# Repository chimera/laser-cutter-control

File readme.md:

# Chimera Laser Cutter Control

**Responsible Adult**: [Randy Hall](https://github.com/randybuildsthings)

This Chimera project provides the project (circuit board, bill of materials, etc.) to provide a Mach3/LinuxCNC capable controller board to drive the laser + the stepper motors that position the cutting beam.

This project borrows *heavily* (read: hours of looking over a PDF schematic) of the very excellent but out-of-stock Laser Cutter Converter board that Chris Jones of [Chris' Circuits](http://www.chriscircuits.com) successfully made and then sold out of repeatedly thanks to Hack-A-Day in 2013.

Well, it's almost 2015 and he doesn't seem to be making it any more. Enter the Chimera!

## Ew, EAGLE CAD

Yeah, it's EAGLE CAD. This design works entirely in their free tier, using just two layers and within the size constraints. We might consider moving it to KiCAD or another PCB layout tool, but for now, it's this.

This project was built from scratch using EAGLE CAD 7. We don't expect that it will work on previous version of the program.

## But, what do I do with this?

Ultimately, we will provide packaged and tagged releases of the Gerber and Excellon files for a given revision. Then you can take those files to your favorite PCB fab and get them made.

For now, you can load up whatever version of EAGLE CAD you can find, and open the `.SCH` and `.BRD` files into the software. Behold! The masterpiece. Now you can use the CAM batch tool to create the Gerber and Excellon files.

Step three... PROFIT!

## Warranty

*There is none.*

If you build and use this board and it burns down your laser cutter, your house, your RV, your office building, or the whole neighborhood, **it's on you bro.** If you don't accept this, then don't use this design. Otherwise, experiment wisely and always have a fire extinguisher handy. And an emergency power shutoff wouldn't hurt either.

The good news is we've now open sourced it, so knock yourself out! (*Note: any reference to knocking oneself out is said here only in jest, and neither Chimera Art Space or the author take any responsibility for anyone who actually takes the imperative literally, thereby effecting blunt force trauma on themselves causing loss of consciousness. This message will self-destruct whenever we get around to editing the Markdown to remove it*)

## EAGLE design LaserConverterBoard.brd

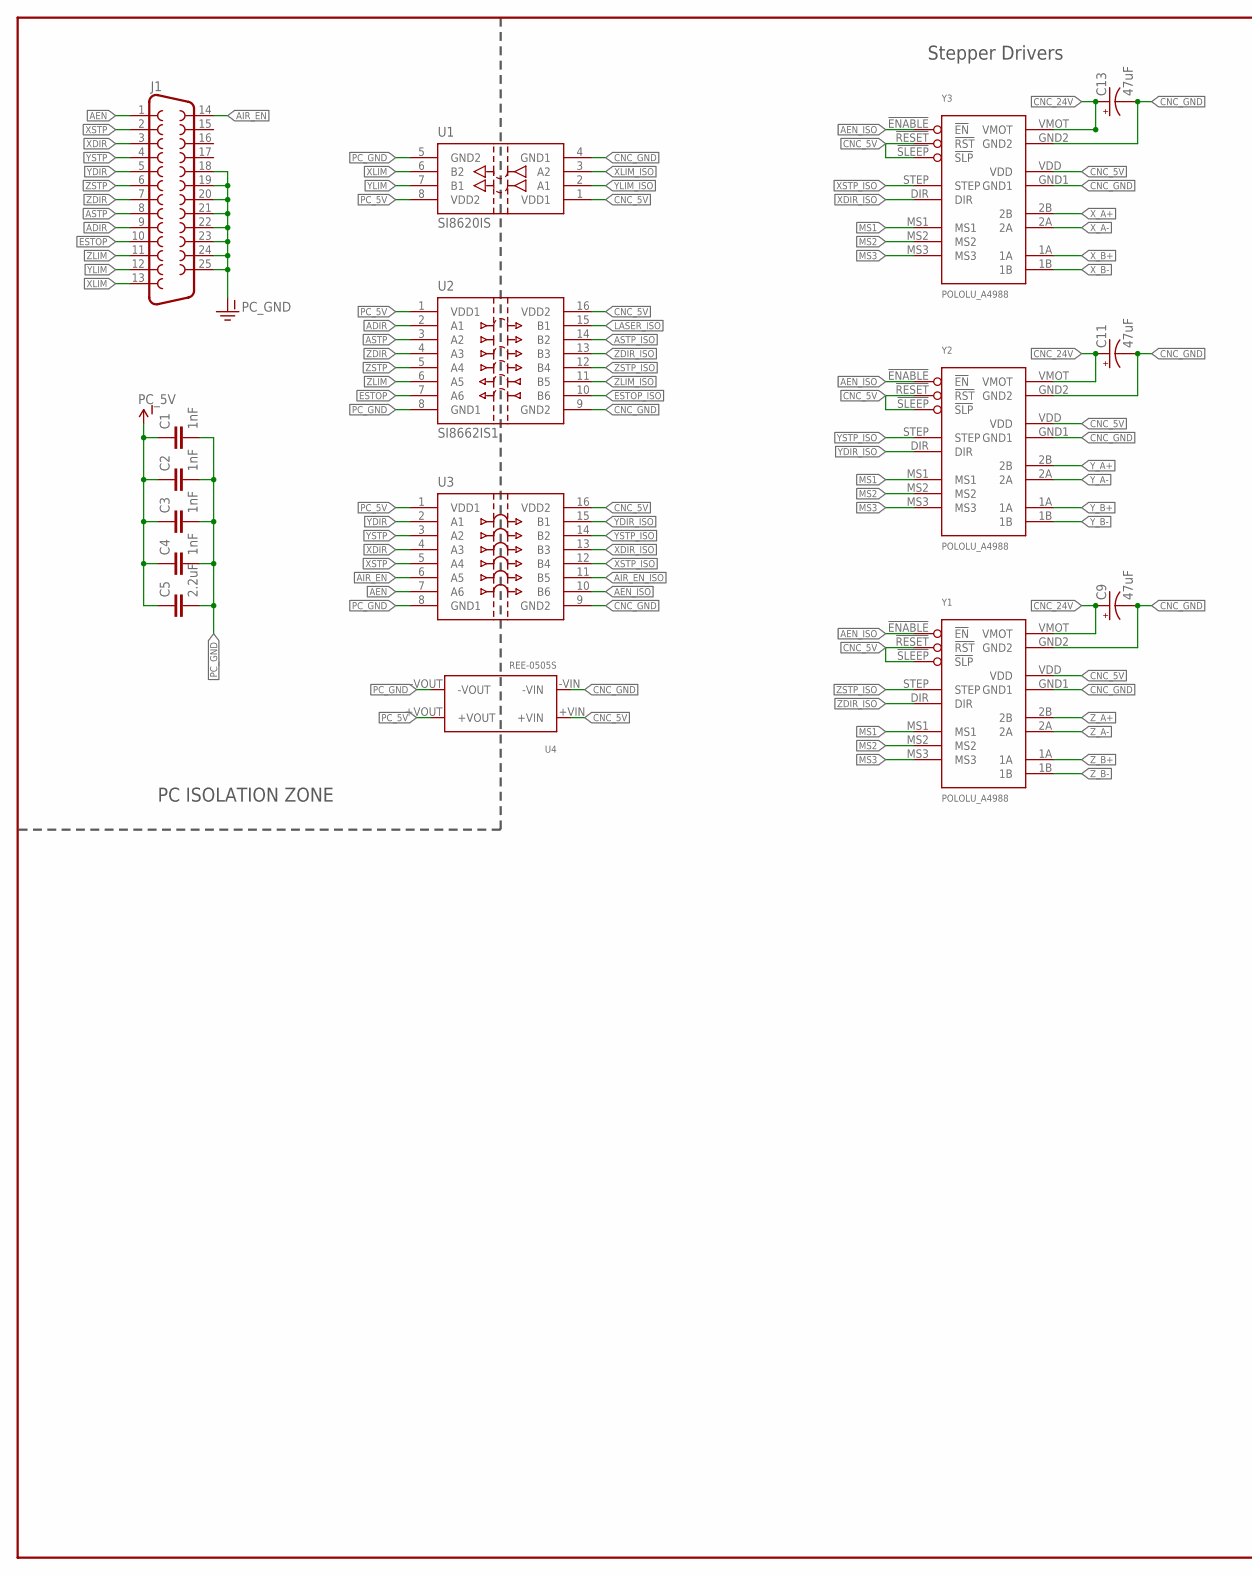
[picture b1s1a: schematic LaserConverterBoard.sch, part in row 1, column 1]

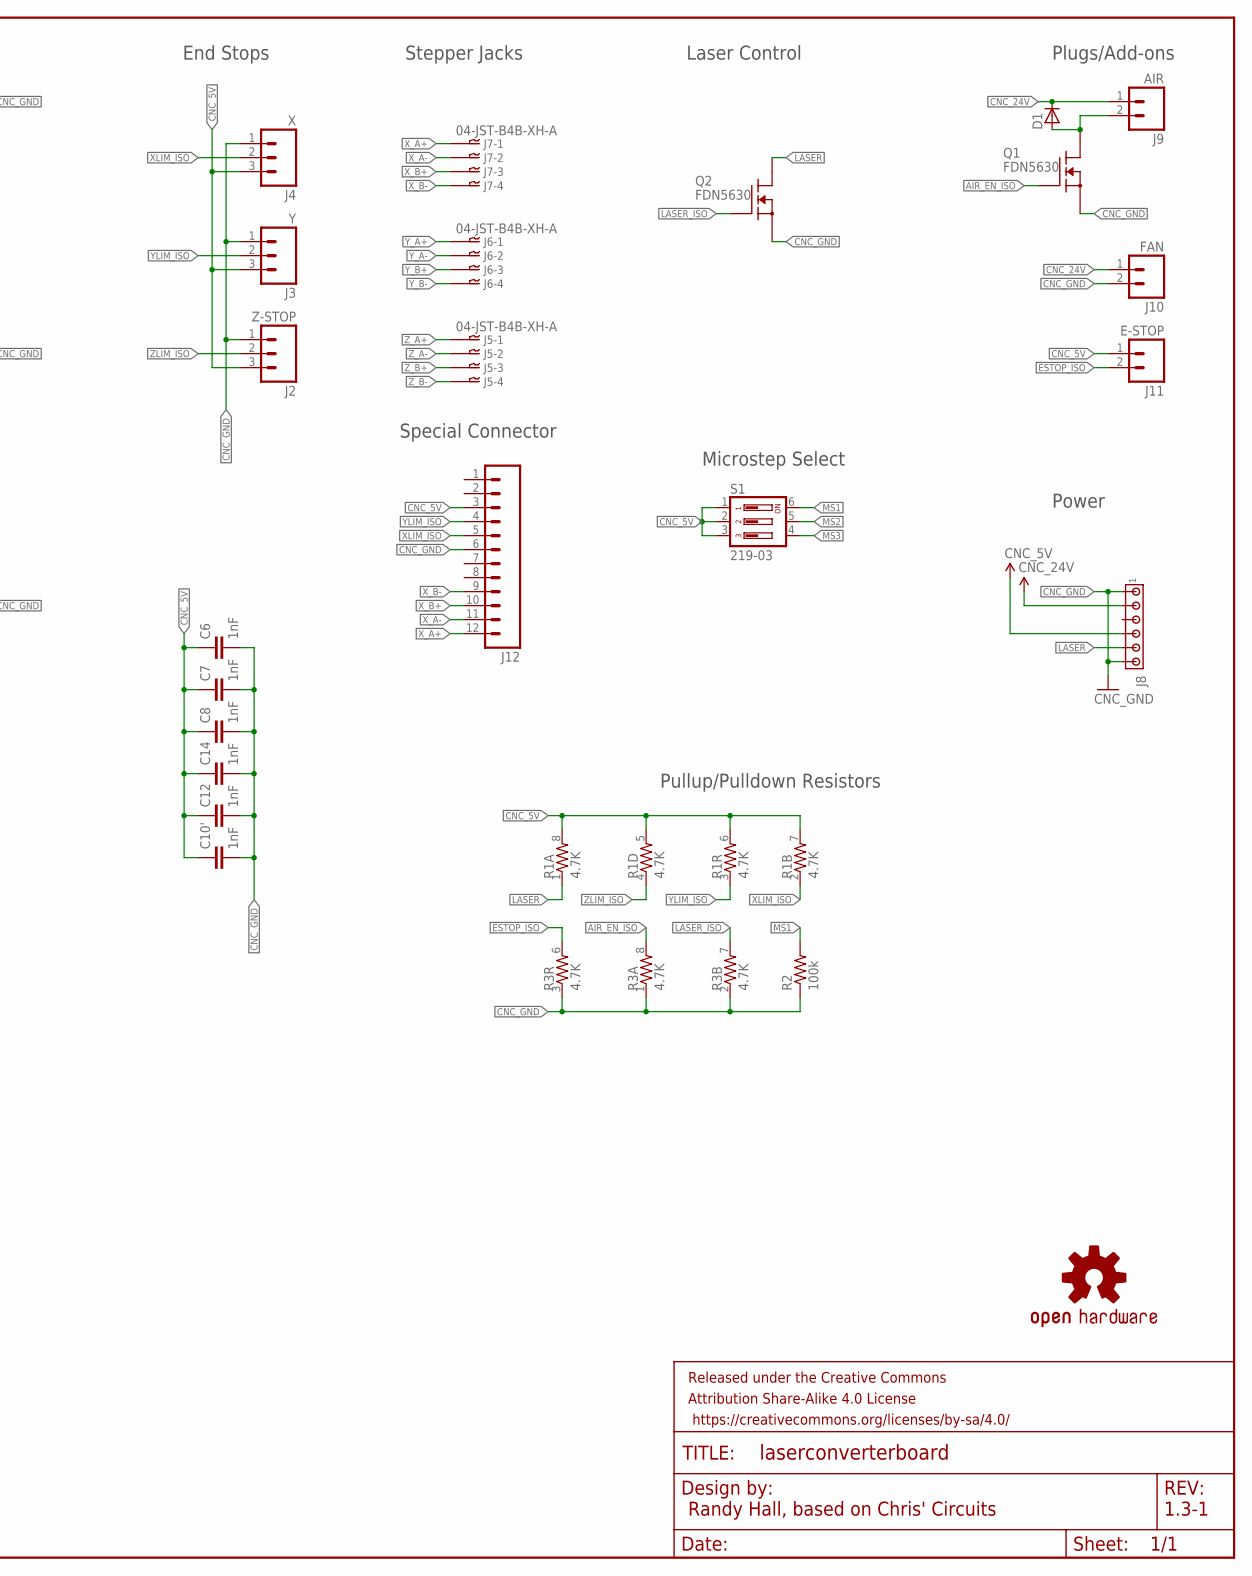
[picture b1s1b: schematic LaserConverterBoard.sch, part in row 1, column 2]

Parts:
C1, C2, C3, C4, C6, C7, C8, C10', C12, C14: 1nF; 0603-CAP
C5: 2.2uF; 0603-CAP
C9, C11, C13: 47uF; PANASONIC_E
D1: D-SOD123; SOD123
FRAME1: FRAME-LEDGER; CREATIVE_COMMONS
J1: F25HP
J2: Z-STOP; 1X03
J3: Y; 1X03
J4: X; 1X03
J5, J6, J7: 04-JST-B4B-XH-A; B4B-XH
J8: MTA06-156; 1X6MTA
J9: AIR; 1X02
J10: FAN; 1X02
J11: E-STOP; 1X02
J12: M12; 12P
LOGO1: OSHW-LOGOS; OSHW-LOGO-S
Q1, Q2: FDN5630; SOT23
R1, R3: 4.7K; 0603-ARV
R2: 100k; 0603-RES
S1: 219-03; CTS-219-03
U1: SI8620IS; SO08
U2: SI8662IS1; SO16
U3: SI8460IS1; SO16
U4: REE-0505S; SIP7
Y1, Y2, Y3: POLOLU_A4988; POLOLU_STEPPER_DRIVER

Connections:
ADIR: J1.9, U2.2 (A1)
AEN: J1.1, U3.7 (A6)
AEN_ISO: U3.10 (B6), Y1.!ENABLE (!EN), Y2.!ENABLE (!EN), Y3.!ENABLE (!EN)
AIR_EN: J1.14, U3.6 (A5)
AIR_EN_ISO: Q1.1 (G), R3.8 (2), U3.11 (B5)
ASTP: J1.8, U2.3 (A2)
ASTP_ISO: U2.14 (B2)
CNC_5V: C6.1, C7.1, C8.1, C10'.1, C12.1, C14.1, J2.3, J3.3, J4.3, J8.4, J11.1, J12.3, R1.5 (2), R1.6 (2), R1.7 (2), R1.8 (2), S1.1, S1.2, S1.3, U1.1 (VDD1), U2.16 (VDD2), U3.16 (VDD2), U4.+VIN, Y1.!RESET (!RST), Y1.!SLEEP (!SLP), Y1.VDD, Y2.!RESET (!RST), Y2.!SLEEP (!SLP), Y2.VDD, Y3.!RESET (!RST), Y3.!SLEEP (!SLP), Y3.VDD
CNC_24V: C9.+, C11.+, C13.+, D1.1 (C), J8.2, J9.1, J10.1, Y1.VMOT, Y2.VMOT, Y3.VMOT
CNC_GND: C6.2, C7.2, C8.2, C9.-, C10'.2, C11.-, C12.2, C13.-, C14.2, J2.1, J3.1, J4.1, J8.1, J8.6, J10.2, J12.6, Q1.2 (S), Q2.2 (S), R2.1, R3.1, R3.2 (1), R3.3 (1), U1.4 (GND1), U2.9 (GND2), U3.9 (GND2), U4.-VIN, Y1.GND1, Y1.GND2, Y2.GND1, Y2.GND2, Y3.GND1, Y3.GND2
ESTOP: J1.10, U2.7 (A6)
ESTOP_ISO: J11.2, R3.6 (2), U2.10 (B6)
LASER: J8.5, Q2.3 (D), R1.1
LASER_ISO: Q2.1 (G), R3.7 (2), U2.15 (B1)
MS1: R2.2, S1.6, Y1.MS1, Y2.MS1, Y3.MS1
MS2: S1.5, Y1.MS2, Y2.MS2, Y3.MS2
MS3: S1.4, Y1.MS3, Y2.MS3, Y3.MS3
unnamed: D1.2 (A), J9.2, Q1.3 (D)
PC_5V: C1.1, C2.1, C3.1, C4.1, C5.1, U1.8 (VDD2), U2.1 (VDD1), U3.1 (VDD1), U4.+VOUT
PC_GND: C1.2, C2.2, C3.2, C4.2, C5.2, J1.18, J1.19, J1.20, J1.21, J1.22, J1.23, J1.24, J1.25, U1.5 (GND2), U2.8 (GND1), U3.8 (GND1), U4.-VOUT
XDIR: J1.3, U3.4 (A3)
XDIR_ISO: U3.13 (B3), Y3.DIR
XLIM: J1.13, U1.6 (B2)
XLIM_ISO: J4.2, J12.5, R1.2 (1), U1.3 (A2)
XSTP: J1.2, U3.5 (A4)
XSTP_ISO: U3.12 (B4), Y3.STEP
X_A+: J7.P$1, J12.12, Y3.2B
X_A-: J7.P$2, J12.11, Y3.2A
X_B+: J7.P$3, J12.10, Y3.1A
X_B-: J7.P$4, J12.9, Y3.1B
YDIR: J1.5, U3.2 (A1)
YDIR_ISO: U3.15 (B1), Y2.DIR
YLIM: J1.12, U1.7 (B1)
YLIM_ISO: J3.2, J12.4, R1.3 (1), U1.2 (A1)
YSTP: J1.4, U3.3 (A2)
YSTP_ISO: U3.14 (B2), Y2.STEP
Y_A+: J6.P$1, Y2.2B
Y_A-: J6.P$2, Y2.2A
Y_B+: J6.P$3, Y2.1A
Y_B-: J6.P$4, Y2.1B
ZDIR: J1.7, U2.4 (A3)
ZDIR_ISO: U2.13 (B3), Y1.DIR
ZLIM: J1.11, U2.6 (A5)
ZLIM_ISO: J2.2, R1.4 (1), U2.11 (B5)
ZSTP: J1.6, U2.5 (A4)
ZSTP_ISO: U2.12 (B4), Y1.STEP
Z_A+: J5.P$1, Y1.2B
Z_A-: J5.P$2, Y1.2A
Z_B+: J5.P$3, Y1.1A
Z_B-: J5.P$4, Y1.1B

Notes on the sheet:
Randy Hall, based on Chris' Circuits
1.3-1
PC ISOLATION ZONE
Pullup/Pulldown Resistors
Stepper Drivers
Plugs/Add-ons
Power
Microstep Select
End Stops
Stepper Jacks
Laser Control
Special Connector

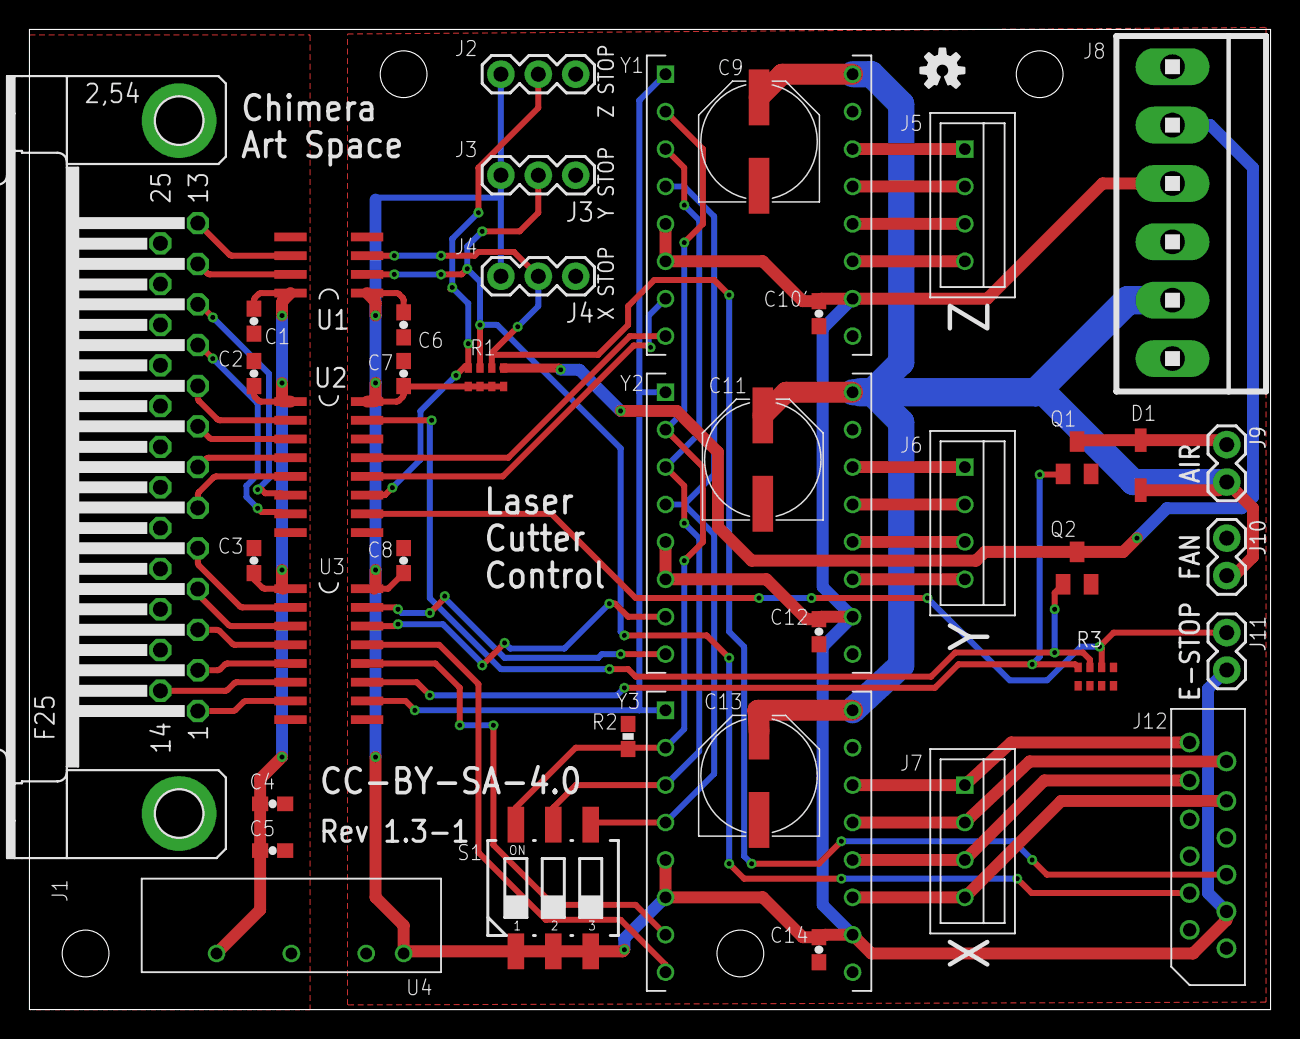
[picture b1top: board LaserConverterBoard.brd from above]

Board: 2 copper layers, 84.3 x 66.5 mm, 42 parts (0 on the bottom side), 49 nets.

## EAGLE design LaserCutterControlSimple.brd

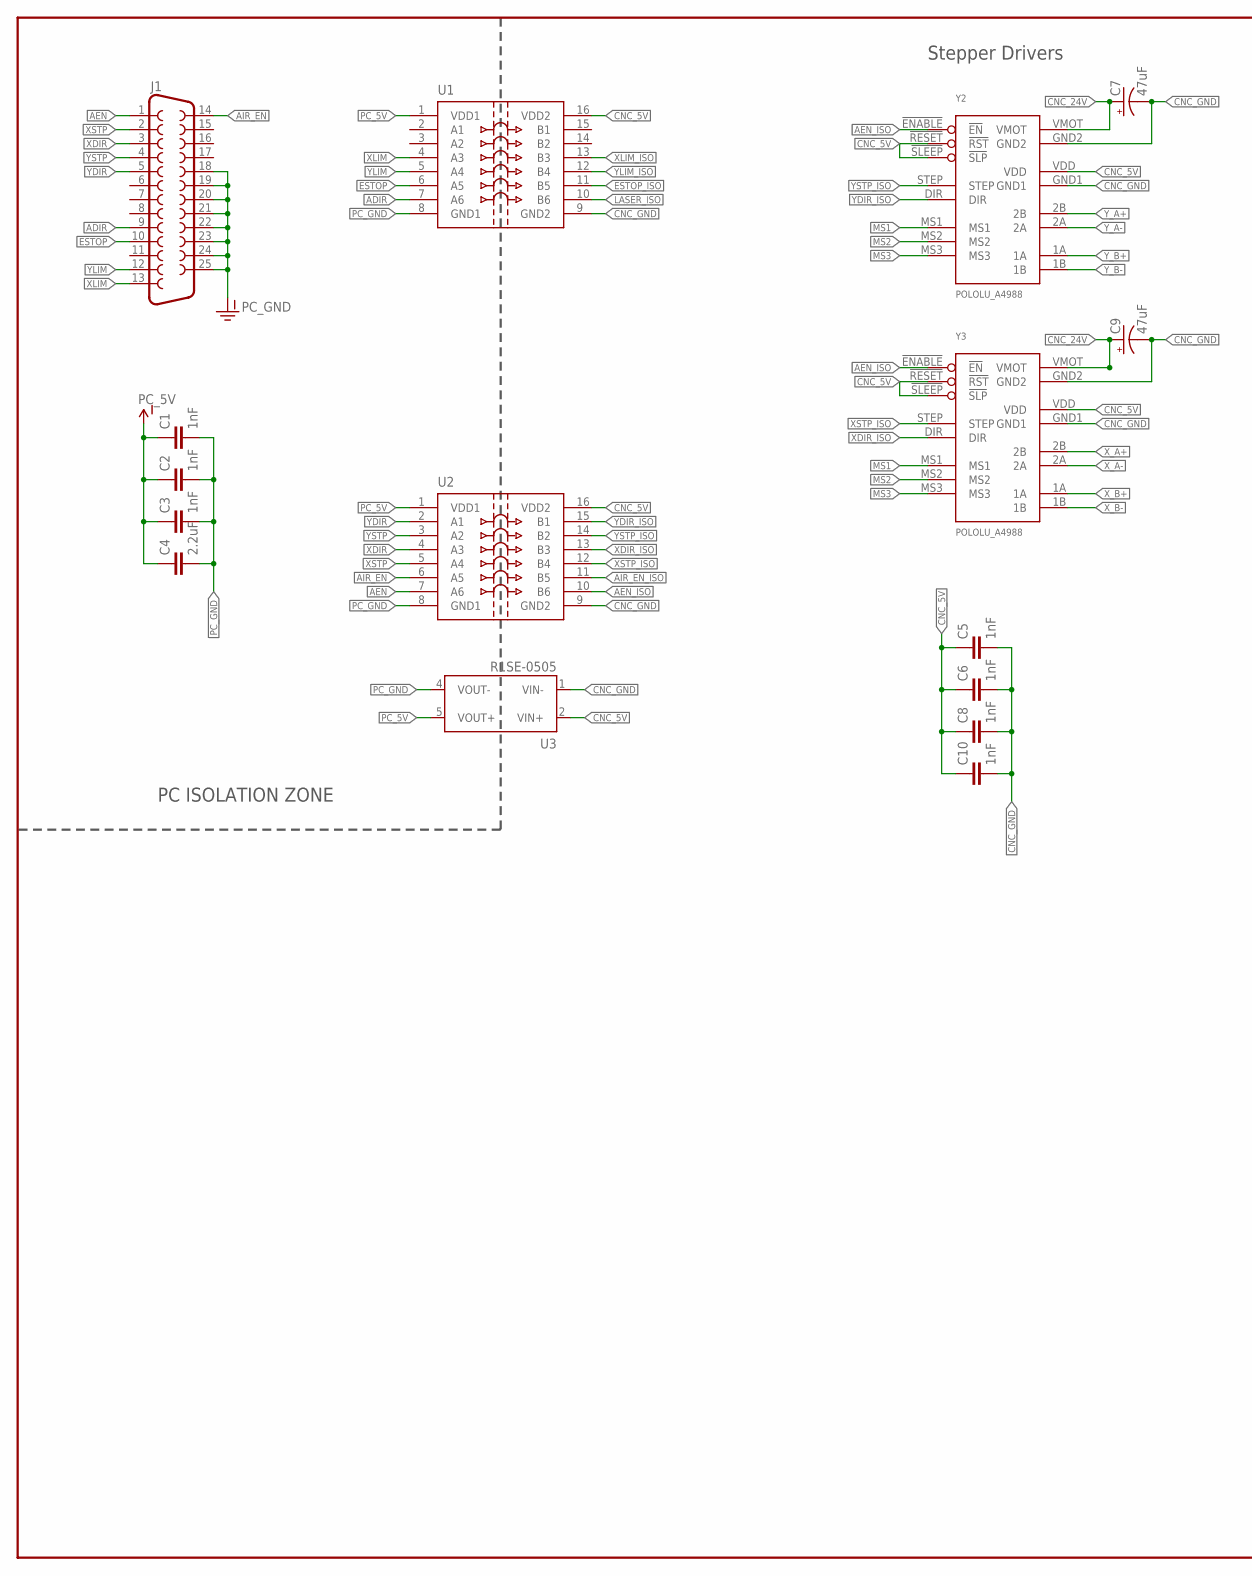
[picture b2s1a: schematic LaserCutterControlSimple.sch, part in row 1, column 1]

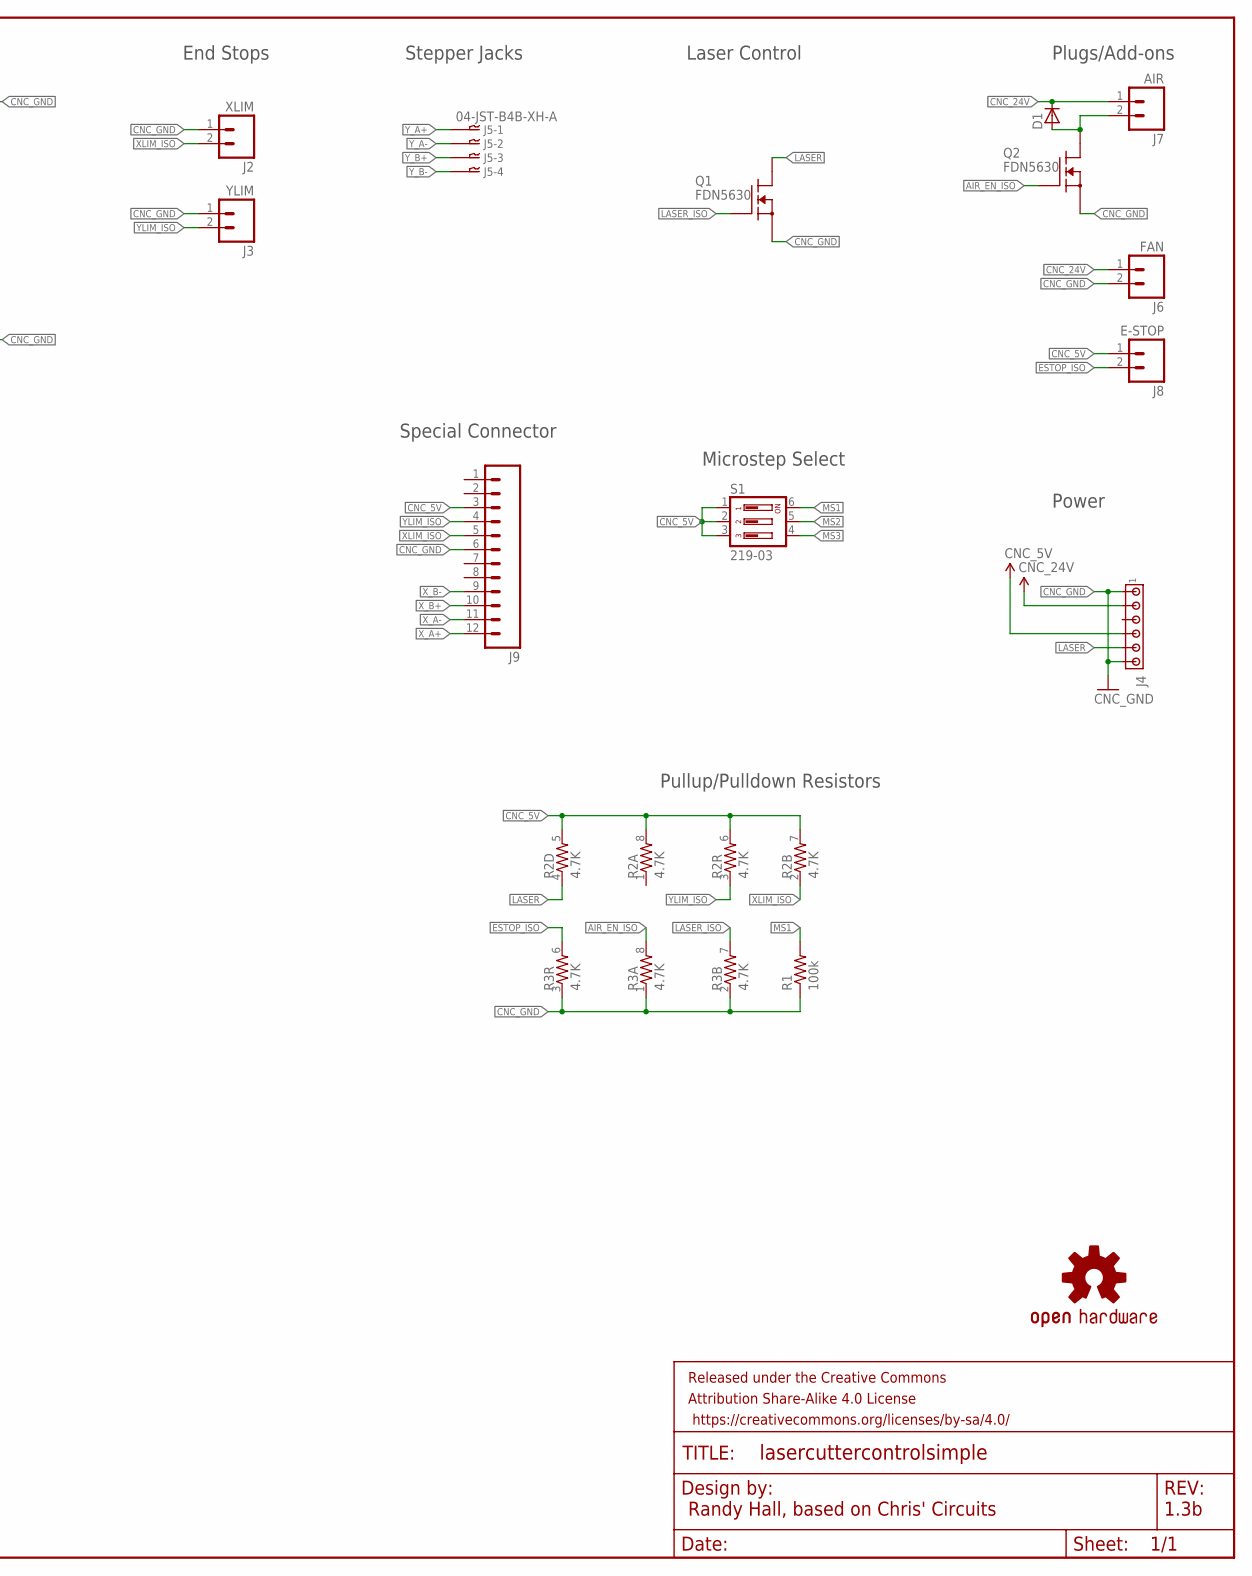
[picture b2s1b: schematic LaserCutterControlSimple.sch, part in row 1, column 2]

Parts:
C1, C2, C3, C5, C6, C8, C10: 1nF; 0603-CAP
C4: 2.2uF; 0603-CAP
C7, C9: 47uF; PANASONIC_E
D1: D-SOD123; SOD123
FRAME1: FRAME-LEDGER; CREATIVE_COMMONS
J1: F25HP
J2: XLIM; 1X02
J3: YLIM; 1X02
J4: MTA06-156; 1X6MTA
J5: 04-JST-B4B-XH-A; B4B-XH
J6: FAN; 1X02
J7: AIR; 1X02
J8: E-STOP; 1X02
J9: M12; 12P
LOGO1: OSHW-LOGOM; OSHW-LOGO-M
Q1, Q2: FDN5630; SOT23
R1: 100k; 0603-RES
R2, R3: 4.7K; 0603-ARV
S1: 219-03; CTS-219-03
U1, U2: SI8460IS1; SO16
U3: R1SE-0505; SMD5
Y2, Y3: POLOLU_A4988; POLOLU_STEPPER_DRIVER

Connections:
ADIR: J1.9, U1.7 (A6)
AEN: J1.1, U2.7 (A6)
AEN_ISO: U2.10 (B6), Y2.!ENABLE (!EN), Y3.!ENABLE (!EN)
AIR_EN: J1.14, U2.6 (A5)
AIR_EN_ISO: Q2.1 (G), R3.8 (2), U2.11 (B5)
CNC_5V: C5.1, C6.1, C8.1, C10.1, J4.4, J8.1, J9.3, R2.5 (2), R2.6 (2), R2.7 (2), R2.8 (2), S1.1, S1.2, S1.3, U1.16 (VDD2), U2.16 (VDD2), U3.2 (VIN+), Y2.!RESET (!RST), Y2.!SLEEP (!SLP), Y2.VDD, Y3.!RESET (!RST), Y3.!SLEEP (!SLP), Y3.VDD
CNC_24V: C7.+, C9.+, D1.1 (C), J4.2, J6.1, J7.1, Y2.VMOT, Y3.VMOT
CNC_GND: C5.2, C6.2, C7.-, C8.2, C9.-, C10.2, J2.1, J3.1, J4.1, J4.6, J6.2, J9.6, Q1.2 (S), Q2.2 (S), R1.1, R3.1, R3.2 (1), R3.3 (1), U1.9 (GND2), U2.9 (GND2), U3.1 (VIN-), Y2.GND1, Y2.GND2, Y3.GND1, Y3.GND2
ESTOP: J1.10, U1.6 (A5)
ESTOP_ISO: J8.2, R3.6 (2), U1.11 (B5)
LASER: J4.5, Q1.3 (D), R2.4 (1)
LASER_ISO: Q1.1 (G), R3.7 (2), U1.10 (B6)
MS1: R1.2, S1.6, Y2.MS1, Y3.MS1
MS2: S1.5, Y2.MS2, Y3.MS2
MS3: S1.4, Y2.MS3, Y3.MS3
unnamed: D1.2 (A), J7.2, Q2.3 (D)
PC_5V: C1.1, C2.1, C3.1, C4.1, U1.1 (VDD1), U2.1 (VDD1), U3.5 (VOUT+)
PC_GND: C1.2, C2.2, C3.2, C4.2, J1.18, J1.19, J1.20, J1.21, J1.22, J1.23, J1.24, J1.25, U1.8 (GND1), U2.8 (GND1), U3.4 (VOUT-)
XDIR: J1.3, U2.4 (A3)
XDIR_ISO: U2.13 (B3), Y3.DIR
XLIM: J1.13, U1.4 (A3)
XLIM_ISO: J2.2, J9.5, R2.2 (1), U1.13 (B3)
XSTP: J1.2, U2.5 (A4)
XSTP_ISO: U2.12 (B4), Y3.STEP
X_A+: J9.12, Y3.2B
X_A-: J9.11, Y3.2A
X_B+: J9.10, Y3.1A
X_B-: J9.9, Y3.1B
YDIR: J1.5, U2.2 (A1)
YDIR_ISO: U2.15 (B1), Y2.DIR
YLIM: J1.12, U1.5 (A4)
YLIM_ISO: J3.2, J9.4, R2.3 (1), U1.12 (B4)
YSTP: J1.4, U2.3 (A2)
YSTP_ISO: U2.14 (B2), Y2.STEP
Y_A+: J5.P$1, Y2.2B
Y_A-: J5.P$2, Y2.2A
Y_B+: J5.P$3, Y2.1A
Y_B-: J5.P$4, Y2.1B

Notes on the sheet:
Randy Hall, based on Chris' Circuits
1.3b
PC ISOLATION ZONE
Pullup/Pulldown Resistors
Stepper Drivers
Plugs/Add-ons
Power
Microstep Select
End Stops
Stepper Jacks
Laser Control
Special Connector

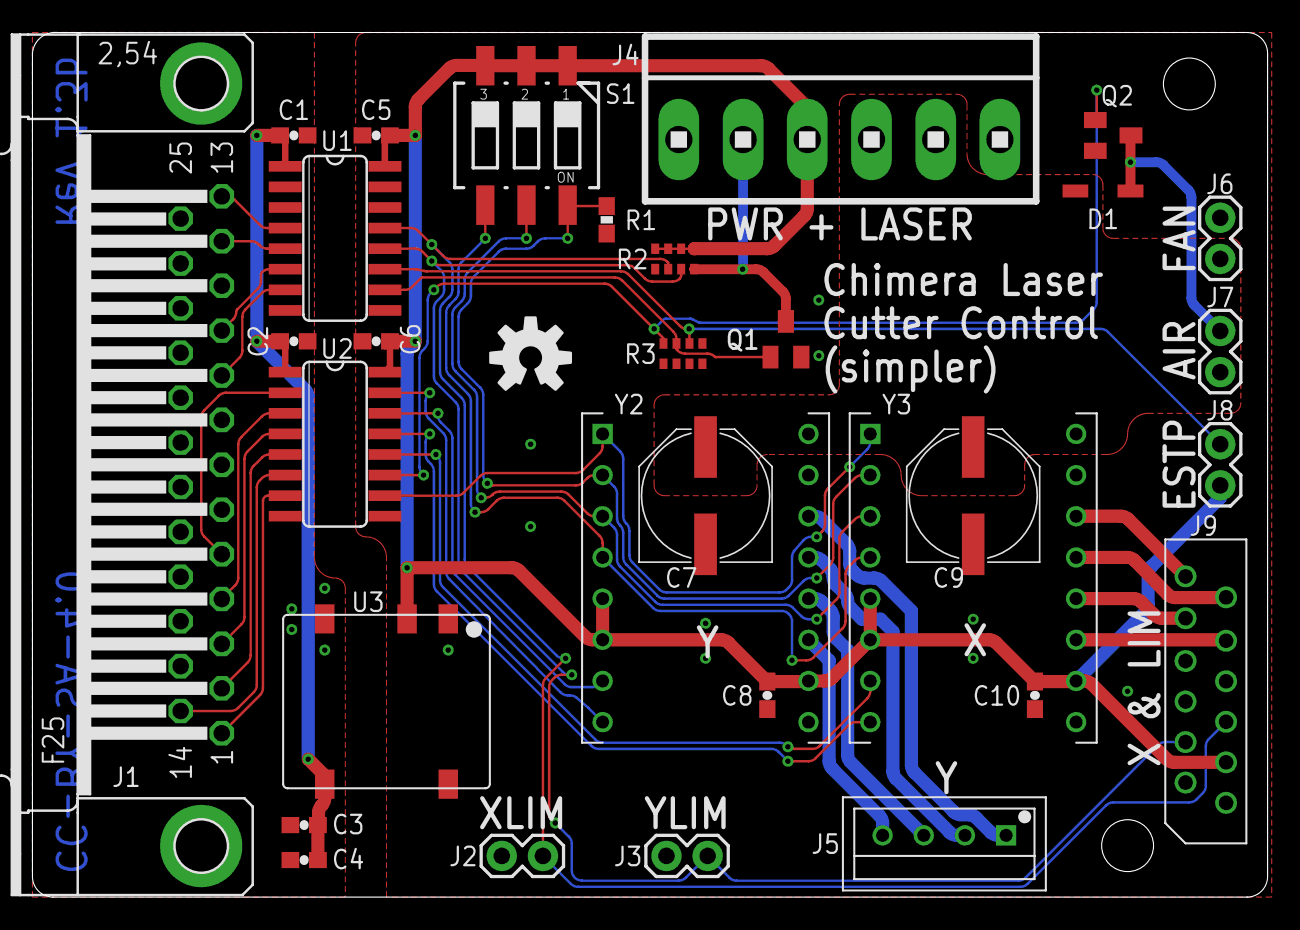
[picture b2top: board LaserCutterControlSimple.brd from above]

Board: 2 copper layers, 76.2 x 53.3 mm, 33 parts (0 on the bottom side), 38 nets.

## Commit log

2014-11-26 Initial commit to the repo
2014-11-26 Hand routing of board 1.3 complete. Still needs silk screening done.
2014-11-26 Silk screen done, could use a Chimera Logo on it, IMO
2014-11-27 Added Silk Screen for name and CC/OSHW licensing
2014-11-27 Adding alternate, stripped-down version of the board. Fewer parts, smaller footprint, cheaper to fabricate.
2014-11-27 Updating gitignore to keep the cruft out.
2014-11-30 Minor dumb change because it was very early in the morning when I finished the simplified board design. Silk screen and connector change to better match laser cutter connections.
2014-11-30 More silkscreen and plug fixes to full-size board
2014-12-01 More tweaks to 1.3-1 and 1.3b, some repositioning and swapping of parts for layout, now that I've seen what the inside of the laser cutter looks like. Added pinouts for X and Y limits to the simple b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
2014-12-01 Okay, now the pins that need to feed back to the CNC controller actually can get there. What a mess. Bill of materials will now have three individual parts. I can see why Chris did it with nine Si842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

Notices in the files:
LaserConverterBoard.brd:
CC-BY-SA-4.0
parts and their libraries:
SparkFun-Capacitors: Licensing: Creative Commons ShareAlike 4.0 International - https://creativecommons.org/licenses/by-sa/4.0
SparkFun-Aesthetics: Released under the Creative Commons Attribution Share-Alike 4.0 License
SparkFun-Aesthetics: https://creativecommons.org/licenses/by-sa/4.0
